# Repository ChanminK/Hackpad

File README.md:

# Duck v1 Hackpad
Hackpad for blueprint!

This is a small 9-key macropad with a rotary encoder, OLED display, and SK6812 MINI-E RGB LEDs.  

I usually only make CAD models, so this was my first time properly making a PCB-really fun!!!

Designed to be a compact editing/drawing pad.

## Features
- 3×3 layout 
- EC11 rotary encoder 
- 0.91" 128×32 SSD1306 OLED display 
- 4× SK6812 MINI-E RGB LEDs 
- Seeed XIAO RP2040

## CAD Model
Made in Fusion360. Everything fits together with heatset inserts and M3 screws.  

---

## PCB

Schematic | PCB Front | PCB Back
:-------:|:---------:|:--------:
 |  | 

Cost estimate:

Rendered PCB:

---

## Firmware Overview
This macropad uses QMK-style firmware! (Still need to make it though...)

---

## BOM
Every part used for this macropad is listed below (also available in `BOM.csv`):

- 9× MX mechanical switches
- 9× DSA keycaps (or any MX-compatible cap)
- 9× 1N4148 diodes (through-hole)
- 1× XIAO RP2040
- 1× EC11 rotary encoder (KY-040 module or bare EC11)
- 1× 0.91" 128×32 OLED Display (GND–VCC–SCL–SDA)
- 4× SK6812 MINI-E addressable RGB LEDs
- 6× M3×5×4 mm heatset inserts
- 6× M3×16 mm screws
- 1× Custom PCB
- 1× 3D-printed case (top + bottom)

---

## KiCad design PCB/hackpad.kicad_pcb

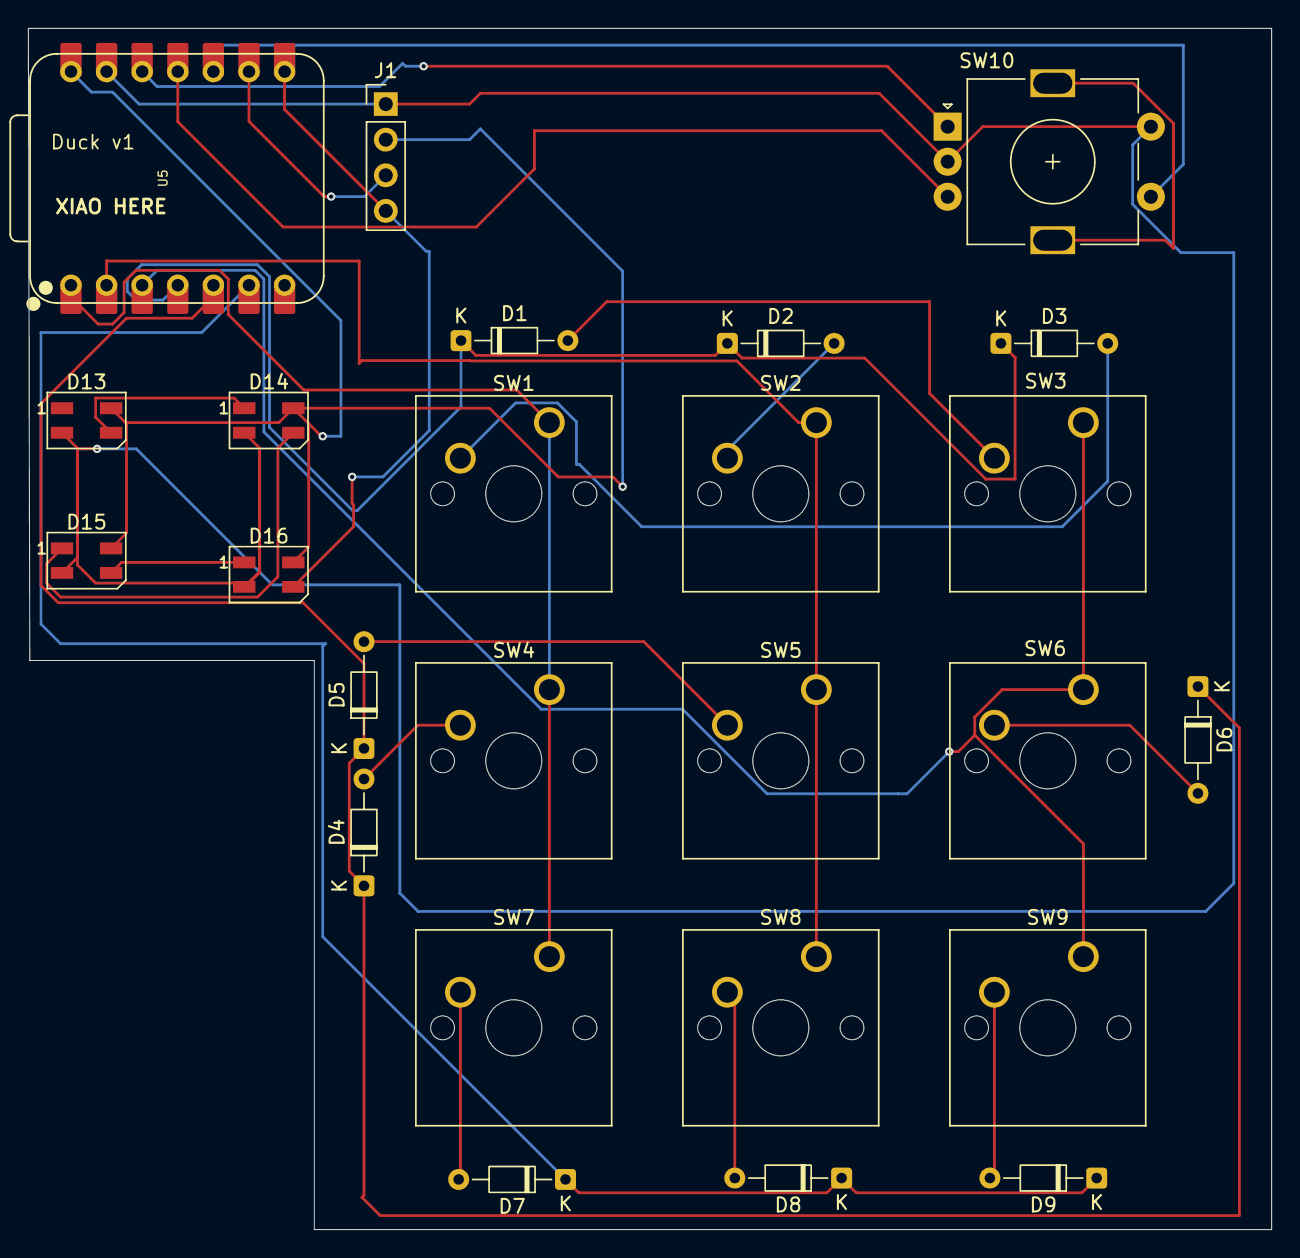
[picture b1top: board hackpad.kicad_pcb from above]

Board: 2 copper layers, 88.7 x 85.7 mm, 25 parts (0 on the bottom side), 25 nets.

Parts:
D1, D2, D3, D4, D5, D6, D7, D8, D9: 1N4148WT; D_DO-34_SOD68_P7.62mm_Horizontal
D13, D14, D15, D16: SK6812MINI; LED_SK6812MINI_PLCC4_3.5x3.5mm_P1.75mm
J1: Conn_01x04_MountingPin; PinHeader_1x04_P2.54mm_Vertical
SW1, SW2, SW3, SW4, SW5, SW6, SW7, SW8, SW9: SW_Push_45deg; SW_Cherry_MX_1.00u_PCB
SW10: RotaryEncoder_Switch_MP; RotaryEncoder_Alps_EC11E-Switch_Vertical_H20mm
U5: XIAO-RP2040-DIP

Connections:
+5V: D13.4 (VDD), D14.4 (VDD), D15.4 (VDD), D16.4 (VDD), J1.2, U5.14 (VBUS)
Col1: SW1.1, SW4.1, SW7.1, U5.1 (GPIO26/ADC0/A0)
Col2: SW2.1, SW5.1, SW8.1, U5.2 (GPIO27/ADC1/A1)
Col3: SW3.1, SW6.1, SW9.1, U5.3 (GPIO28/ADC2/A2)
GND: D13.2 (VSS), D14.2 (VSS), D15.2 (VSS), D16.2 (VSS), J1.1, SW10.C, SW10.S2, U5.13 (GND)
unnamed: D1.2 (A), SW3.2
unnamed: D2.2 (A), SW2.2
unnamed: D3.2 (A), SW1.2
unnamed: D4.2 (A), SW4.2
unnamed: D5.2 (A), SW5.2
unnamed: D6.2 (A), SW6.2
unnamed: D7.2 (A), SW7.2
unnamed: D8.2 (A), SW8.2
unnamed: D9.2 (A), SW9.2
unnamed: D13.3 (DIN), D14.1 (DOUT)
unnamed: D14.3 (DIN), D15.1 (DOUT)
unnamed: D15.3 (DIN), D16.1 (DOUT)
unnamed: D16.3 (DIN), J1.4, U5.8 (GPIO1/RX)
unnamed: J1.3, U5.9 (GPIO2/SCK)
unnamed: SW10.A, U5.12 (3V3)
unnamed: SW10.B, U5.11 (GPIO3/MOSI)
unnamed: SW10.S1, U5.10 (GPIO4/MISO)
Row1: D1.1 (K), D2.1 (K), D3.1 (K), U5.4 (GPIO29/ADC3/A3)
Row2: D4.1 (K), D5.1 (K), D6.1 (K), U5.5 (GPIO6/SDA)
Row3: D7.1 (K), D8.1 (K), D9.1 (K), U5.6 (GPIO7/SCL)

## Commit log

2025-12-03 done!
